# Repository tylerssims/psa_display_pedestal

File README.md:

# psa_display_pedestal
 Project files for a digital psa card display.

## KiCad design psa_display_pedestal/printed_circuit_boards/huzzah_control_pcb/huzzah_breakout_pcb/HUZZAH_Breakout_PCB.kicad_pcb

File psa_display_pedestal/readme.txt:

this project folder is organized with the following folders:
-3d_models
	-.stl and .3mf model files 
-datasheets
	-datasheets for components used
-drawings
	-.dwg files generated from cad files
-images
	-misc project images
-spreadsheets
	-excel sheets for various budgets, BOMs, analysis, etc.
-system_diagrams
	-2D flow charts showing system configuratiopns and performance

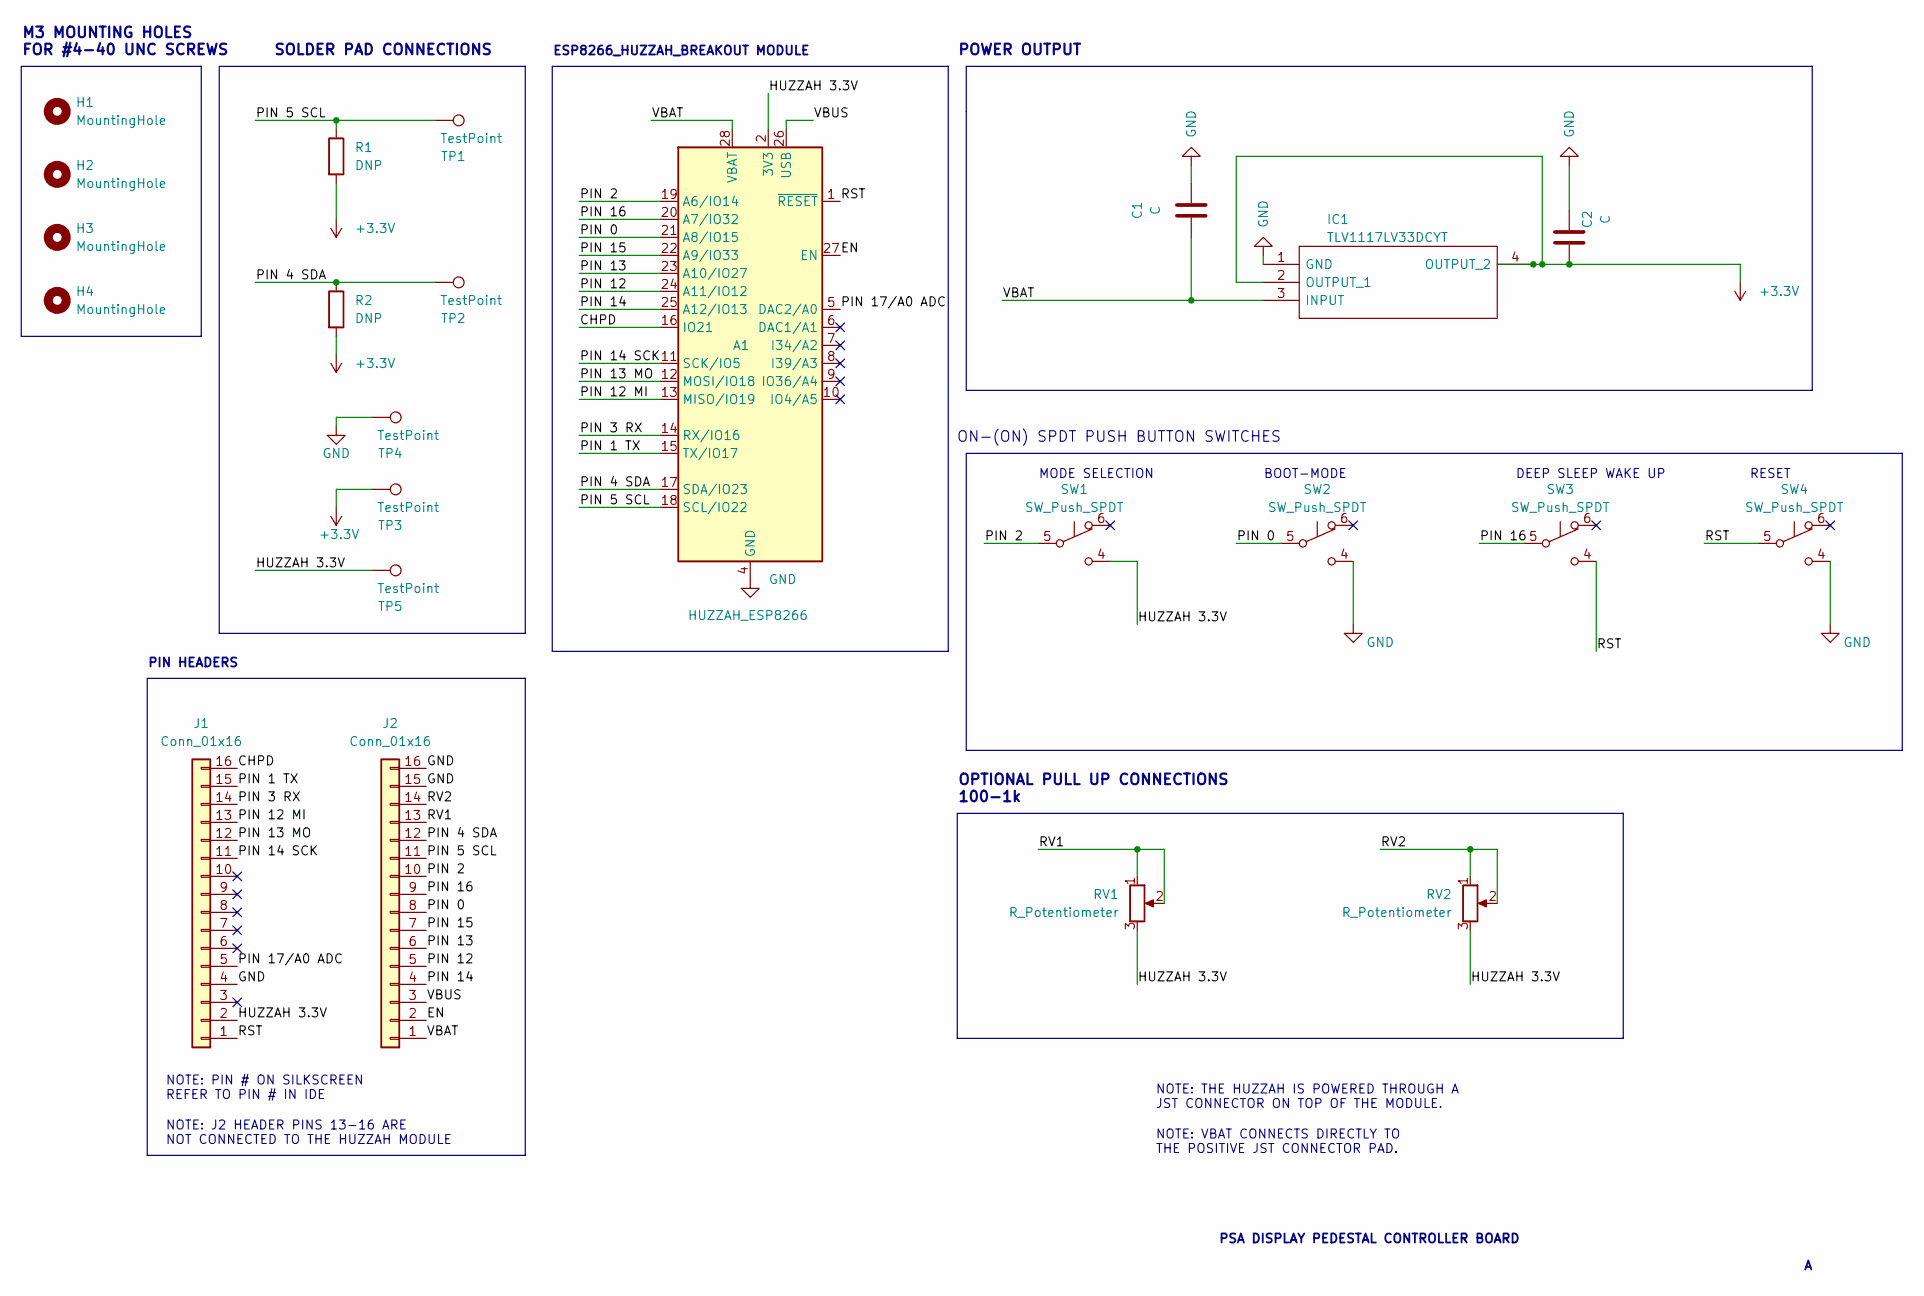
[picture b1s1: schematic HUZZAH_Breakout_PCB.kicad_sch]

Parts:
A1: HUZZAH_ESP8266; Adafruit_Feather
C1, C2: C; C_0805_2012Metric_Pad1.18x1.45mm_HandSolder
H1, H2, H3, H4: MountingHole; MountingHole_3.2mm_M3
IC1: TLV1117LV33DCYT; SOT230P700X180-4N; Mouser Part Number 595-TLV1117LV33DCYT
J1, J2: Conn_01x16; PinHeader_1x16_P2.54mm_Vertical
R1, R2: DNP; R_0805_2012Metric_Pad1.20x1.40mm_HandSolder
RV1, RV2: R_Potentiometer; 3352T1104LF
SW1, SW2, SW3, SW4: SW_Push_SPDT; SW_NKK_GW12LJP
TP1, TP2, TP3, TP4, TP5: TestPoint; SolderWirePad_1x01_SMD_5x10mm

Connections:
+3.3V: C2.1, IC1.2 (OUTPUT_1), IC1.4 (OUTPUT_2), R1.2, R2.2, TP3.1
/CHPD: A1.16 (IO21), J1.16
/EN: A1.27 (EN), J2.2
/HUZZAH 3.3V: A1.2 (3V3), J1.2, RV1.3, RV2.3, SW1.4 (C), TP5.1
/PIN 0: A1.21 (A8/IO15), J2.8, SW2.5 (B)
/PIN 1 TX: A1.15 (TX/IO17), J1.15
/PIN 2: A1.19 (A6/IO14), J2.10, SW1.5 (B)
/PIN 3 RX: A1.14 (RX/IO16), J1.14
/PIN 4 SDA: A1.17 (SDA/IO23), J2.12, R2.1, TP2.1
/PIN 5 SCL: A1.18 (SCL/IO22), J2.11, R1.1, TP1.1
/PIN 12: A1.24 (A11/IO12), J2.5
/PIN 12 MI: A1.13 (MISO/IO19), J1.13
/PIN 13: A1.23 (A10/IO27), J2.6
/PIN 13 MO: A1.12 (MOSI/IO18), J1.12
/PIN 14: A1.25 (A12/IO13), J2.4
/PIN 14 SCK: A1.11 (SCK/IO5), J1.11
/PIN 15: A1.22 (A9/IO33), J2.7
/PIN 16: A1.20 (A7/IO32), J2.9, SW3.5 (B)
/PIN 17/A0 ADC: A1.5 (DAC2/A0), J1.5
/RST: A1.1 (~RESET), J1.1, SW3.4 (C), SW4.5 (B)
/RV1: J2.13, RV1.1, RV1.2
/RV2: J2.14, RV2.1, RV2.2
/VBAT: A1.28 (VBAT), C1.2, IC1.3 (INPUT), J2.1
/VBUS: A1.26 (USB), J2.3
GND: A1.4 (GND), C1.1, C2.2, IC1.1 (GND), J1.4, J2.15, J2.16, SW2.4 (C), SW4.4 (C), TP4.1

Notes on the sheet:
PSA DISPLAY PEDESTAL CONTROLLER BOARD
RESET
BOOT-MODE
SOLDER PAD CONNECTIONS
POWER OUTPUT
OPTIONAL PULL UP CONNECTIONS 100-1k
MODE SELECTION
ESP8266_HUZZAH_BREAKOUT MODULE
NOTE: J2 HEADER PINS 13-16 ARE NOT CONNECTED TO THE HUZZAH MODULE
NOTE: PIN # ON SILKSCREEN REFER TO PIN # IN IDE
PIN HEADERS
NOTE: THE HUZZAH IS POWERED THROUGH A JST CONNECTOR ON TOP OF THE MODULE.
DEEP SLEEP WAKE UP
ON-(ON) SPDT PUSH BUTTON SWITCHES
NOTE: VBAT CONNECTS DIRECTLY TO THE POSITIVE JST CONNECTOR PAD.
M3 MOUNTING HOLES FOR #4-40 UNC SCREWS

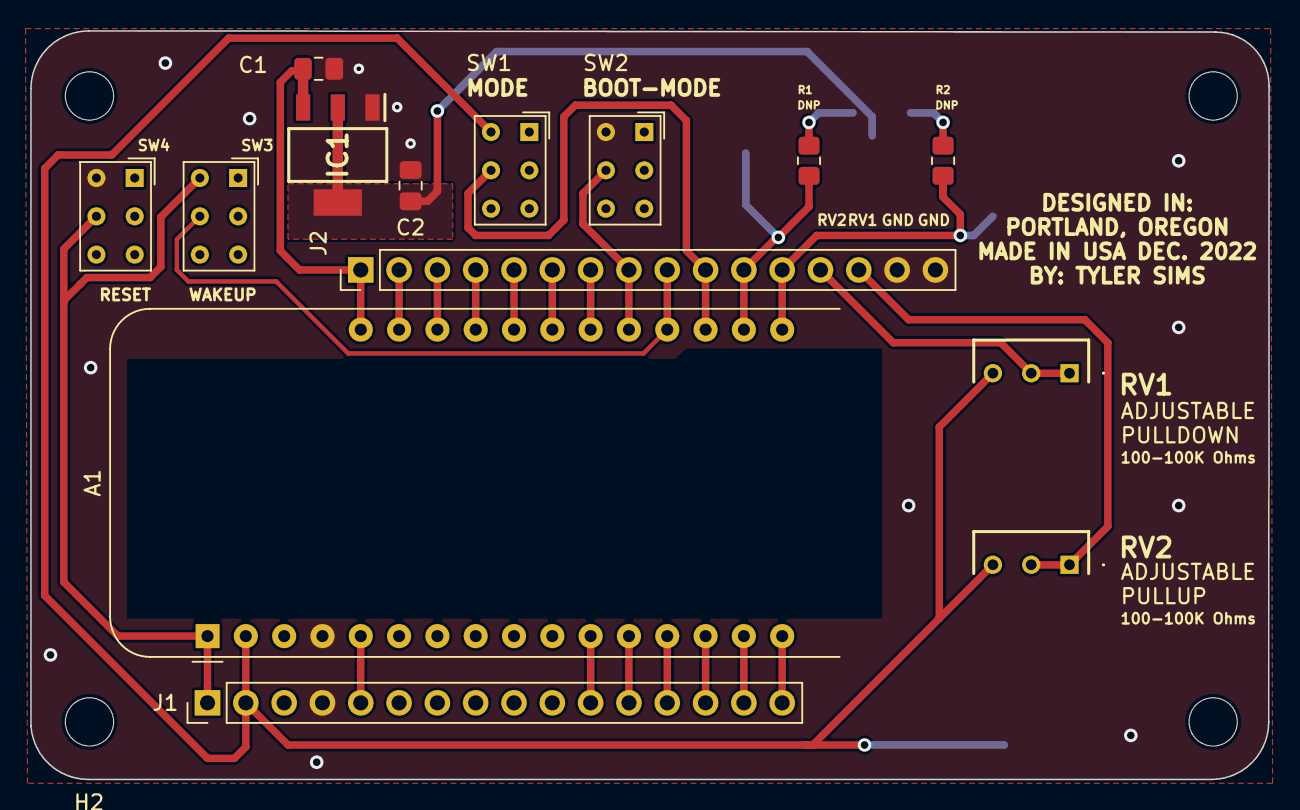
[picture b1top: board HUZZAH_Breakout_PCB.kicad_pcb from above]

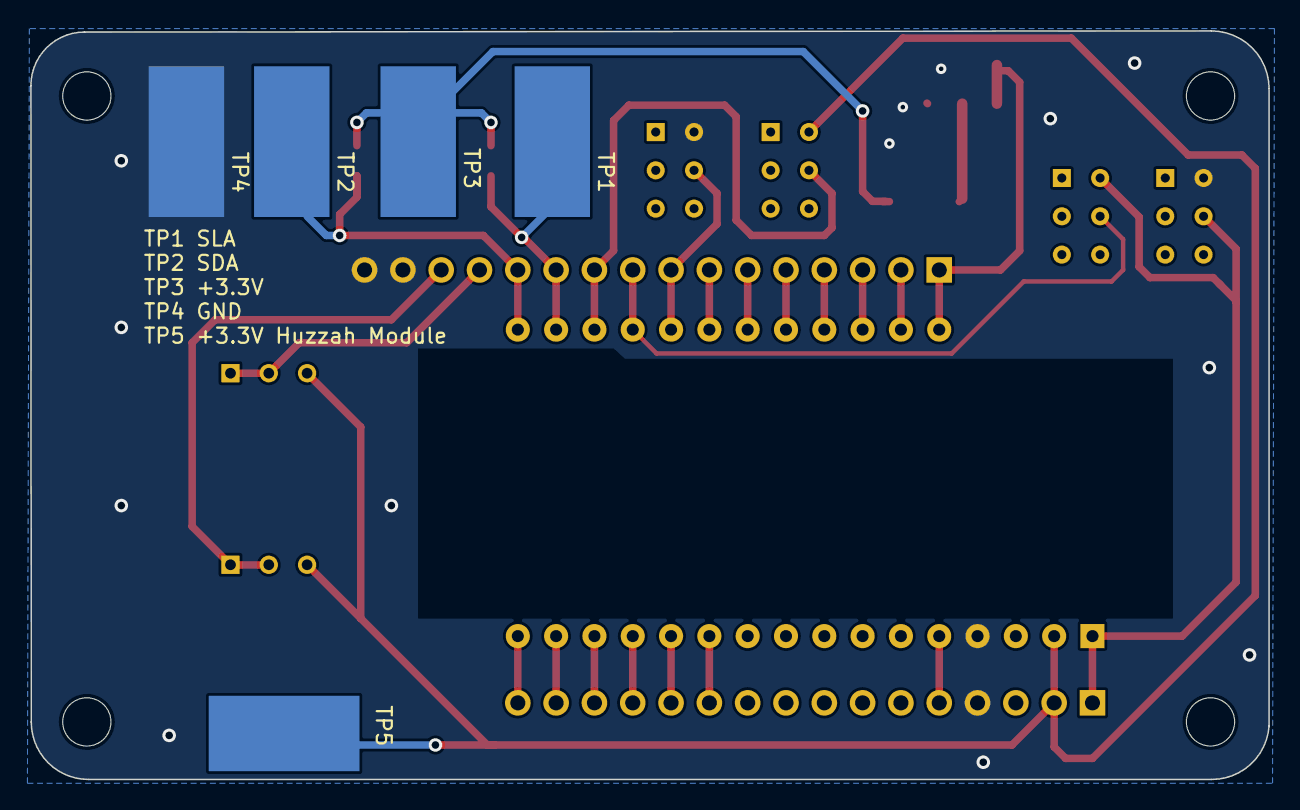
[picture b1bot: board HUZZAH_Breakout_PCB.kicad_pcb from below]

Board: 2 copper layers, 82.1 x 49.6 mm, 23 parts (5 on the bottom side), 25 nets.

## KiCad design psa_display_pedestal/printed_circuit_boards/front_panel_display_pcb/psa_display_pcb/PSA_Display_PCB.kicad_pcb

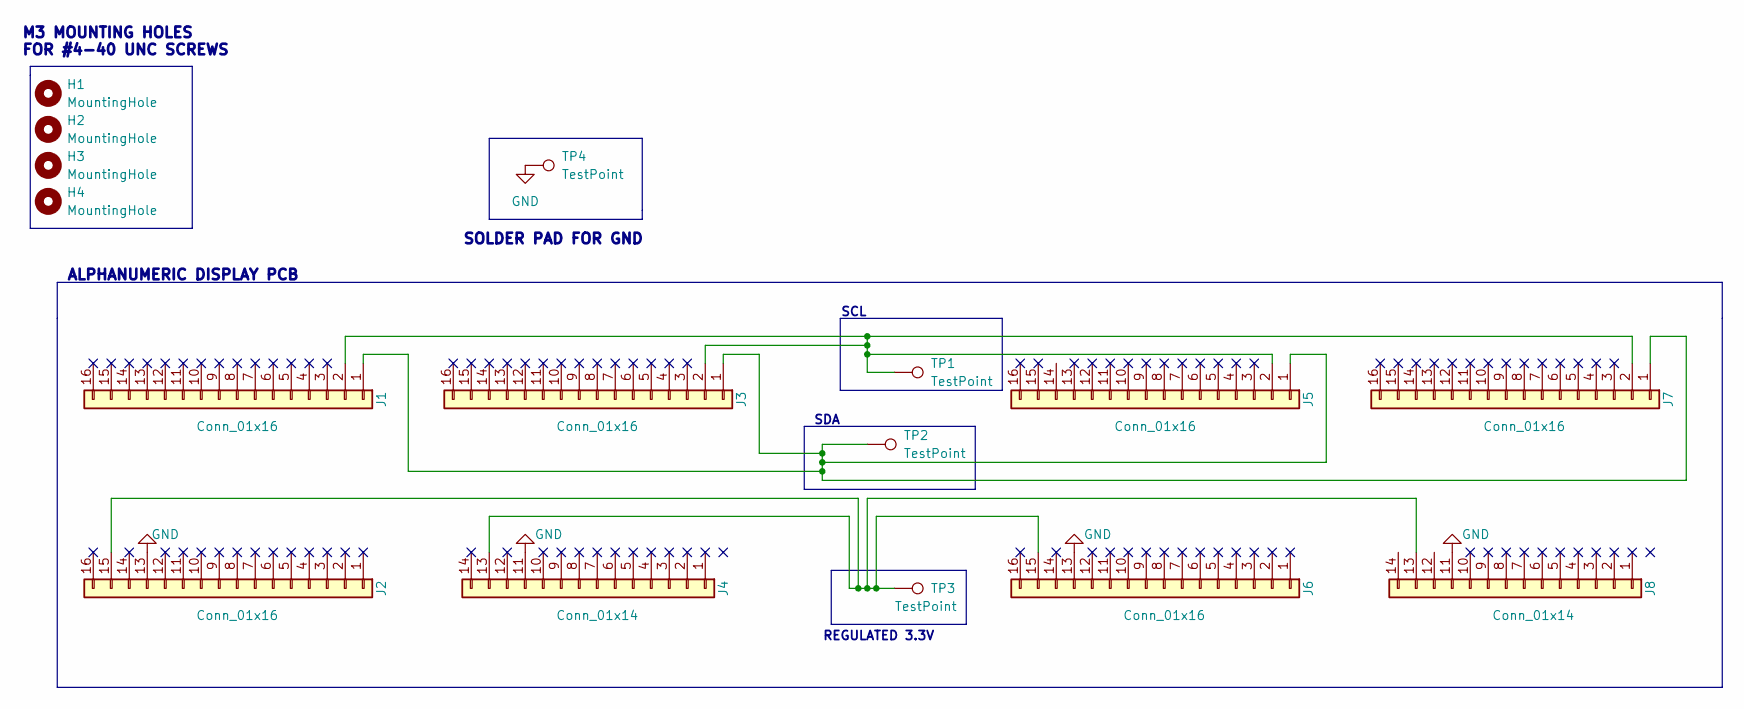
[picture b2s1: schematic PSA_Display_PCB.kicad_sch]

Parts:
H1, H2, H3, H4: MountingHole; MountingHole_3.2mm_M3
J1, J2, J3, J5, J6, J7: Conn_01x16; PinHeader_1x16_P2.54mm_Vertical
J4, J8: Conn_01x14; PinHeader_1x14_P2.54mm_Vertical
TP1, TP2, TP3, TP4: TestPoint; SolderWirePad_1x01_SMD_5x10mm

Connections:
GND: J2.13, J4.11, J6.13, J8.11, TP4.1
unnamed: J2.15, J4.13, J6.15, J8.13, TP3.1
unnamed: J1.2, J3.2, J5.2, J7.2, TP1.1
unnamed: J1.1, J3.1, J5.1, J7.1, TP2.1

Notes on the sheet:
SDA
ALPHANUMERIC DISPLAY PCB
SCL
M3 MOUNTING HOLES FOR #4-40 UNC SCREWS
REGULATED 3.3V
SOLDER PAD FOR GND

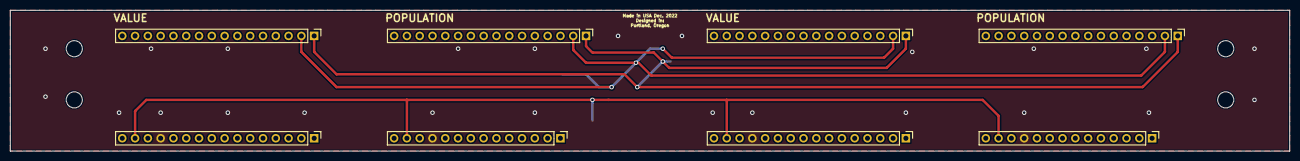
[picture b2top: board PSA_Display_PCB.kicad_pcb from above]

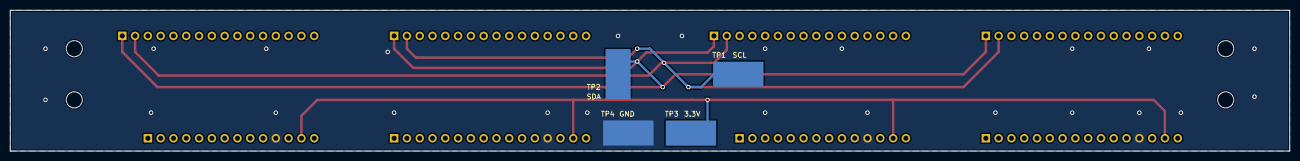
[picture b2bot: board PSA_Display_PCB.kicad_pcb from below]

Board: 2 copper layers, 254.0 x 27.9 mm, 16 parts (4 on the bottom side), 4 nets.

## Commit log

2023-03-03 files after production
